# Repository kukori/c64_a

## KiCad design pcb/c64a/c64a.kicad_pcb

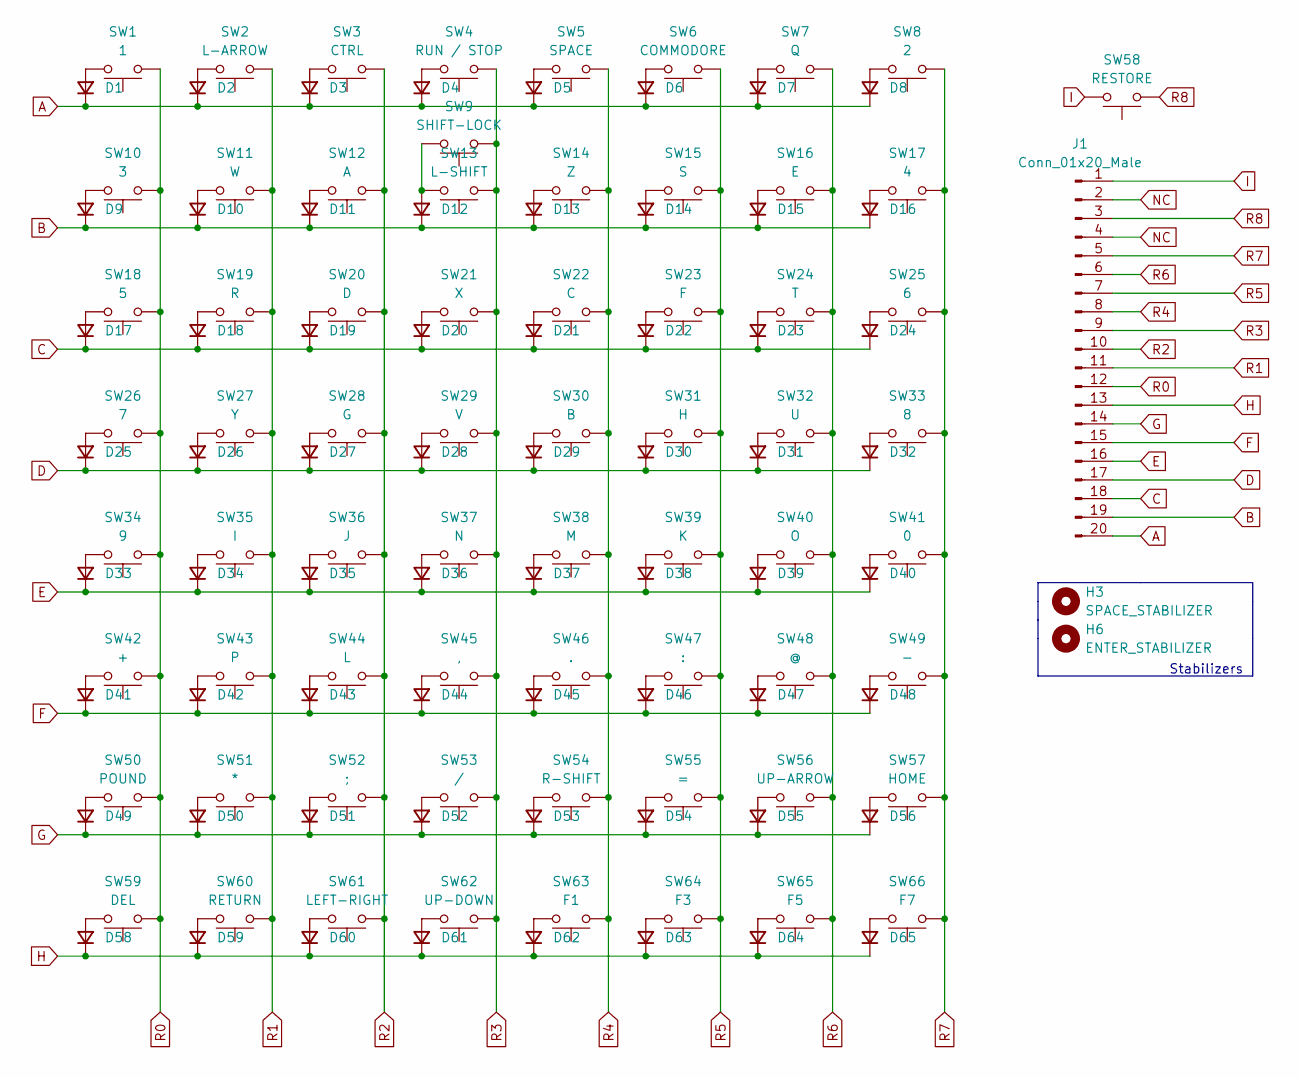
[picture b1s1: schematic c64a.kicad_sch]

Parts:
D1, D2, D3, D4, D5, D6, D7, D8, D9, D10, D11, D12, D13, D14, D15, D16, D17, D18, D19, D20, D21, D22, D23, D24, D25, D26, D27, D28, D29, D30, D31, D32, D33, D34, D35, D36, D37, D38, D39, D40, D41, D42, D43, D44, D45, D46, D47, D48, D49, D50, D51, D52, D53, D54, D55, D56, D58, D59, D60, D61, D62, D63, D64, D65: D_Small; D_SOD-123
H3: SPACE_STABILIZER; Stabilizer_Cherry_MX_9.00u
H6: ENTER_STABILIZER; cherry_mx_stabilizer_2.00u
J1: Conn_01x20_Male; PinHeader_1x20_P2.54mm_Horizontal
SW1: 1; SW_Cherry_MX_1.00u_PCB
SW2: L-ARROW; SW_Cherry_MX_1.00u_PCB
SW3: CTRL; SW_Cherry_MX_1.00u_PCB
SW4: RUN / STOP; SW_Cherry_MX_1.00u_PCB
SW5: SPACE; SW_Cherry_MX_1.00u_PCB
SW6: COMMODORE; SW_Cherry_MX_1.00u_PCB
SW7: Q; SW_Cherry_MX_1.00u_PCB
SW8: 2; SW_Cherry_MX_1.00u_PCB
SW9: SHIFT-LOCK; SW_Cherry_MX_1.00u_PCB
SW10: 3; SW_Cherry_MX_1.00u_PCB
SW11: W; SW_Cherry_MX_1.00u_PCB
SW12: A; SW_Cherry_MX_1.00u_PCB
SW13: L-SHIFT; SW_Cherry_MX_1.00u_PCB
SW14: Z; SW_Cherry_MX_1.00u_PCB
SW15: S; SW_Cherry_MX_1.00u_PCB
SW16: E; SW_Cherry_MX_1.00u_PCB
SW17: 4; SW_Cherry_MX_1.00u_PCB
SW18: 5; SW_Cherry_MX_1.00u_PCB
SW19: R; SW_Cherry_MX_1.00u_PCB
SW20: D; SW_Cherry_MX_1.00u_PCB
SW21: X; SW_Cherry_MX_1.00u_PCB
SW22: C; SW_Cherry_MX_1.00u_PCB
SW23: F; SW_Cherry_MX_1.00u_PCB
SW24: T; SW_Cherry_MX_1.00u_PCB
SW25: 6; SW_Cherry_MX_1.00u_PCB
SW26: 7; SW_Cherry_MX_1.00u_PCB
SW27: Y; SW_Cherry_MX_1.00u_PCB
SW28: G; SW_Cherry_MX_1.00u_PCB
SW29: V; SW_Cherry_MX_1.00u_PCB
SW30: B; SW_Cherry_MX_1.00u_PCB
SW31: H; SW_Cherry_MX_1.00u_PCB
SW32: U; SW_Cherry_MX_1.00u_PCB
SW33: 8; SW_Cherry_MX_1.00u_PCB
SW34: 9; SW_Cherry_MX_1.00u_PCB
SW35: I; SW_Cherry_MX_1.00u_PCB
SW36: J; SW_Cherry_MX_1.00u_PCB
SW37: N; SW_Cherry_MX_1.00u_PCB
SW38: M; SW_Cherry_MX_1.00u_PCB
SW39: K; SW_Cherry_MX_1.00u_PCB
SW40: O; SW_Cherry_MX_1.00u_PCB
SW41: 0; SW_Cherry_MX_1.00u_PCB
SW42: +; SW_Cherry_MX_1.00u_PCB
SW43: P; SW_Cherry_MX_1.00u_PCB
SW44: L; SW_Cherry_MX_1.00u_PCB
SW45: ,; SW_Cherry_MX_1.00u_PCB
SW46: .; SW_Cherry_MX_1.00u_PCB
SW47: :; SW_Cherry_MX_1.00u_PCB
SW48: @; SW_Cherry_MX_1.00u_PCB
SW49: -; SW_Cherry_MX_1.00u_PCB
SW50: POUND; SW_Cherry_MX_1.00u_PCB
SW51: *; SW_Cherry_MX_1.00u_PCB
SW52: ;; SW_Cherry_MX_1.00u_PCB
SW53: /; SW_Cherry_MX_1.00u_PCB
SW54: R-SHIFT; SW_Cherry_MX_1.00u_PCB
SW55: =; SW_Cherry_MX_1.00u_PCB
SW56: UP-ARROW; SW_Cherry_MX_1.00u_PCB
SW57: HOME; SW_Cherry_MX_1.00u_PCB
SW58: RESTORE; SW_Cherry_MX_1.00u_PCB
SW59: DEL; SW_Cherry_MX_1.00u_PCB
SW60: RETURN; SW_Cherry_MX_1.00u_PCB
SW61: LEFT-RIGHT; SW_Cherry_MX_1.00u_PCB
SW62: UP-DOWN; SW_Cherry_MX_1.00u_PCB
SW63: F1; SW_Cherry_MX_1.00u_PCB
SW64: F3; SW_Cherry_MX_1.00u_PCB
SW65: F5; SW_Cherry_MX_1.00u_PCB
SW66: F7; SW_Cherry_MX_1.00u_PCB

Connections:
A: D1.1 (K), D2.1 (K), D3.1 (K), D4.1 (K), D5.1 (K), D6.1 (K), D7.1 (K), D8.1 (K), J1.20
B: D9.1 (K), D10.1 (K), D11.1 (K), D12.1 (K), D13.1 (K), D14.1 (K), D15.1 (K), D16.1 (K), J1.19
C: D17.1 (K), D18.1 (K), D19.1 (K), D20.1 (K), D21.1 (K), D22.1 (K), D23.1 (K), D24.1 (K), J1.18
D: D25.1 (K), D26.1 (K), D27.1 (K), D28.1 (K), D29.1 (K), D30.1 (K), D31.1 (K), D32.1 (K), J1.17
E: D33.1 (K), D34.1 (K), D35.1 (K), D36.1 (K), D37.1 (K), D38.1 (K), D39.1 (K), D40.1 (K), J1.16
F: D41.1 (K), D42.1 (K), D43.1 (K), D44.1 (K), D45.1 (K), D46.1 (K), D47.1 (K), D48.1 (K), J1.15
G: D49.1 (K), D50.1 (K), D51.1 (K), D52.1 (K), D53.1 (K), D54.1 (K), D55.1 (K), D56.1 (K), J1.14
H: D58.1 (K), D59.1 (K), D60.1 (K), D61.1 (K), D62.1 (K), D63.1 (K), D64.1 (K), D65.1 (K), J1.13
I: J1.1, SW58.2
NC: J1.2, J1.4
unnamed: D1.2 (A), SW1.2
unnamed: D2.2 (A), SW2.2
unnamed: D3.2 (A), SW3.2
unnamed: D4.2 (A), SW4.2
unnamed: D5.2 (A), SW5.2
unnamed: D6.2 (A), SW6.2
unnamed: D7.2 (A), SW7.2
unnamed: D8.2 (A), SW8.2
unnamed: D9.2 (A), SW10.2
unnamed: D10.2 (A), SW11.2
unnamed: D11.2 (A), SW12.2
unnamed: D12.2 (A), SW9.2, SW13.2
unnamed: D13.2 (A), SW14.2
unnamed: D14.2 (A), SW15.2
unnamed: D15.2 (A), SW16.2
unnamed: D16.2 (A), SW17.2
unnamed: D17.2 (A), SW18.2
unnamed: D18.2 (A), SW19.2
unnamed: D19.2 (A), SW20.2
unnamed: D20.2 (A), SW21.2
unnamed: D21.2 (A), SW22.2
unnamed: D22.2 (A), SW23.2
unnamed: D23.2 (A), SW24.2
unnamed: D24.2 (A), SW25.2
unnamed: D25.2 (A), SW26.2
unnamed: D26.2 (A), SW27.2
unnamed: D27.2 (A), SW28.2
unnamed: D28.2 (A), SW29.2
unnamed: D29.2 (A), SW30.2
unnamed: D30.2 (A), SW31.2
unnamed: D31.2 (A), SW32.2
unnamed: D32.2 (A), SW33.2
unnamed: D33.2 (A), SW34.2
unnamed: D34.2 (A), SW35.2
unnamed: D35.2 (A), SW36.2
unnamed: D36.2 (A), SW37.2
unnamed: D37.2 (A), SW38.2
unnamed: D38.2 (A), SW39.2
unnamed: D39.2 (A), SW40.2
unnamed: D40.2 (A), SW41.2
unnamed: D41.2 (A), SW42.2
unnamed: D42.2 (A), SW43.2
unnamed: D43.2 (A), SW44.2
unnamed: D44.2 (A), SW45.2
unnamed: D45.2 (A), SW46.2
unnamed: D46.2 (A), SW47.2
unnamed: D47.2 (A), SW48.2
unnamed: D48.2 (A), SW49.2
unnamed: D49.2 (A), SW50.2
unnamed: D50.2 (A), SW51.2
unnamed: D51.2 (A), SW52.2
unnamed: D52.2 (A), SW53.2
unnamed: D53.2 (A), SW54.2
unnamed: D54.2 (A), SW55.2
unnamed: D55.2 (A), SW56.2
unnamed: D56.2 (A), SW57.2
unnamed: D58.2 (A), SW59.2
unnamed: D59.2 (A), SW60.2
unnamed: D60.2 (A), SW61.2
unnamed: D61.2 (A), SW62.2
unnamed: D62.2 (A), SW63.2
unnamed: D63.2 (A), SW64.2
unnamed: D64.2 (A), SW65.2
unnamed: D65.2 (A), SW66.2
R0: J1.12, SW1.1, SW10.1, SW18.1, SW26.1, SW34.1, SW42.1, SW50.1, SW59.1
R1: J1.11, SW2.1, SW11.1, SW19.1, SW27.1, SW35.1, SW43.1, SW51.1, SW60.1
R2: J1.10, SW3.1, SW12.1, SW20.1, SW28.1, SW36.1, SW44.1, SW52.1, SW61.1
R3: J1.9, SW4.1, SW9.1, SW13.1, SW21.1, SW29.1, SW37.1, SW45.1, SW53.1, SW62.1
R4: J1.8, SW5.1, SW14.1, SW22.1, SW30.1, SW38.1, SW46.1, SW54.1, SW63.1
R5: J1.7, SW6.1, SW15.1, SW23.1, SW31.1, SW39.1, SW47.1, SW55.1, SW64.1
R6: J1.6, SW7.1, SW16.1, SW24.1, SW32.1, SW40.1, SW48.1, SW56.1, SW65.1
R7: J1.5, SW8.1, SW17.1, SW25.1, SW33.1, SW41.1, SW49.1, SW57.1, SW66.1
R8: J1.3, SW58.1

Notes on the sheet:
Stabilizers

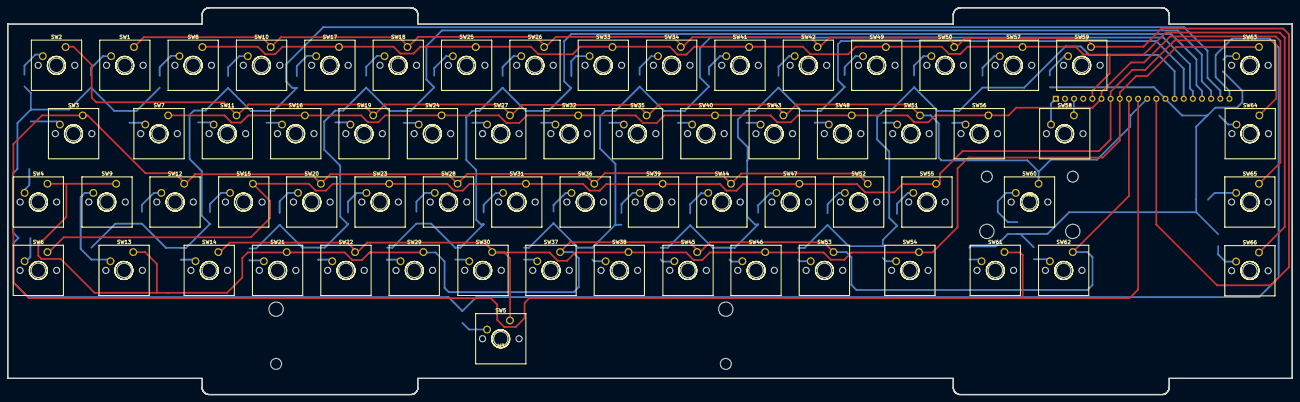
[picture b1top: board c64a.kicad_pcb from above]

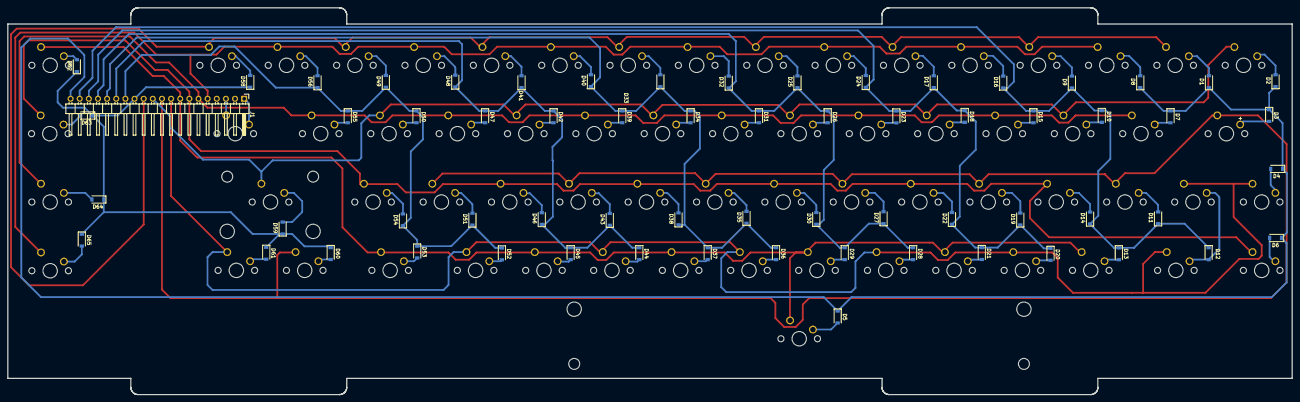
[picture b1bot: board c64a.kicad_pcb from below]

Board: 2 copper layers, 357.0 x 107.5 mm, 133 parts (65 on the bottom side), 83 nets.

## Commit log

2023-01-21 c64_a initial commit
2023-01-22 Switches changed to 5 pin
2023-01-28 Mount covers
2023-02-04 Mount cover + pcb fixes
2023-02-04 Outline fixes
2023-02-19 Fixing spacing issues
